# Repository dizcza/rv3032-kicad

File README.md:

# RV-3032 Kicad PCB

A replacement of the DS3231 with the same board pinout:

| DS3231 | RV3032 | Description                                     |
|--------|--------|-------------------------------------------------|
| GND    | GND    | GND                                             |
| VCC    | VCC    | 2.0-5.5V                                        |
| SDA    | SDA    | I2C SDA                                         |
| SCL    | SCL    | I2C SCL                                         |
| SQW    | CLKOUT | Temperature compensated square wave             |
| 32K    | INT    | DS3231: oscillator clock; RV3032: interrupt pin |

Board dimensions: 14 x 16 mm.

See [schematics.pdf](./schematics.pdf).

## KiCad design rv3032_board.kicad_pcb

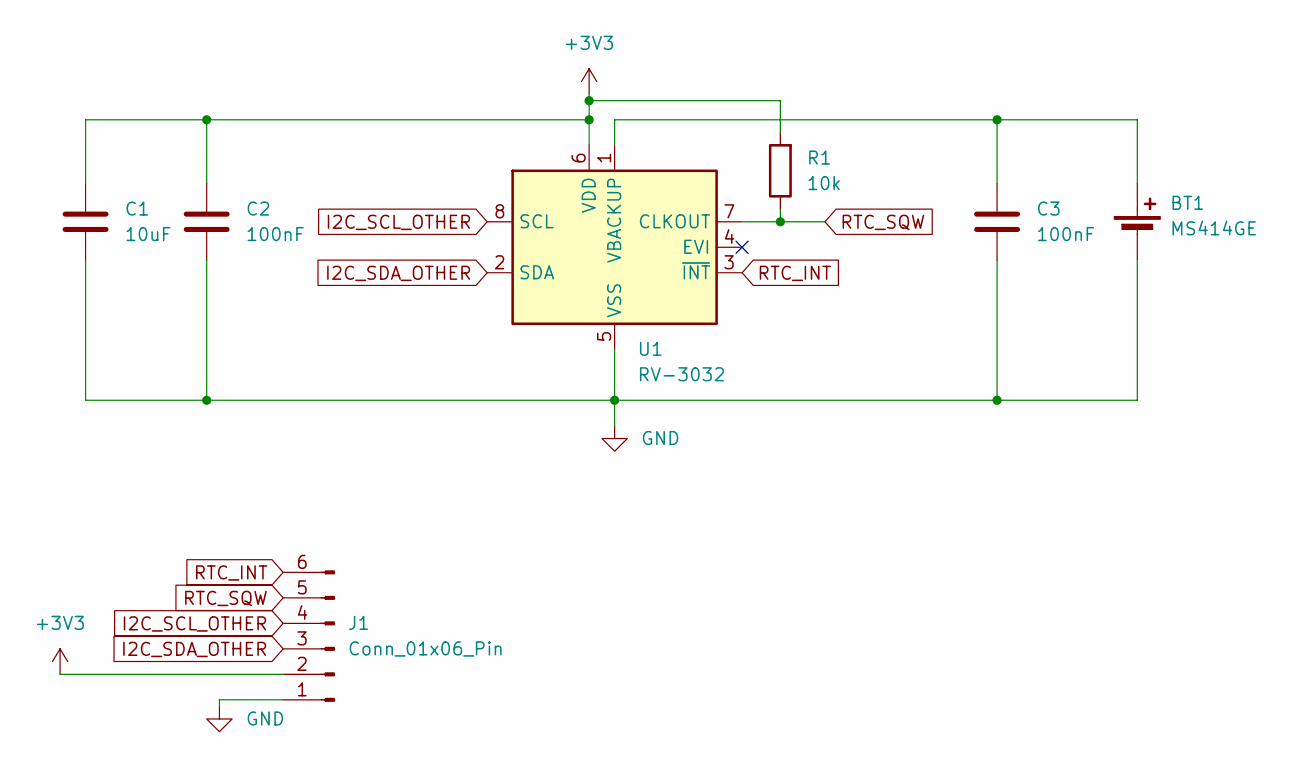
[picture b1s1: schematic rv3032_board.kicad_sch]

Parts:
BT1: MS414GE; BAT_MS414GE-FL26E
C1: 10uF; C_0603_1608Metric; LCSC C19702
C2, C3: 100nF; C_0402_1005Metric; LCSC C1525
J1: Conn_01x06_Pin; PinHeader_1x06_P2.54mm_Horizontal
R1: 10k; R_0402_1005Metric; LCSC C25744
U1: RV-3032; LCSC C5127802

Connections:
+3V3: C1.1, C2.2, J1.2, R1.2, U1.6 (VDD)
GND: BT1.2 (-), C1.2, C2.1, C3.1, J1.1, U1.5 (VSS)
I2C_SCL_OTHER: J1.4, U1.8 (SCL)
I2C_SDA_OTHER: J1.3, U1.2 (SDA)
unnamed: BT1.1 (+), C3.2, U1.1 (VBACKUP)
RTC_INT: J1.6, U1.3 (~INT)
RTC_SQW: J1.5, R1.1, U1.7 (CLKOUT)

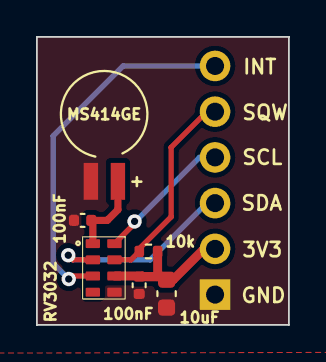
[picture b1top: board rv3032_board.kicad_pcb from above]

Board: 2 copper layers, 14.0 x 16.0 mm, 7 parts (1 on the bottom side), 7 nets.

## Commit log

2024-01-28 v2: replacement DS3231
2024-02-07 v1 ordered
2024-02-07 readme
2024-07-06 3d model
